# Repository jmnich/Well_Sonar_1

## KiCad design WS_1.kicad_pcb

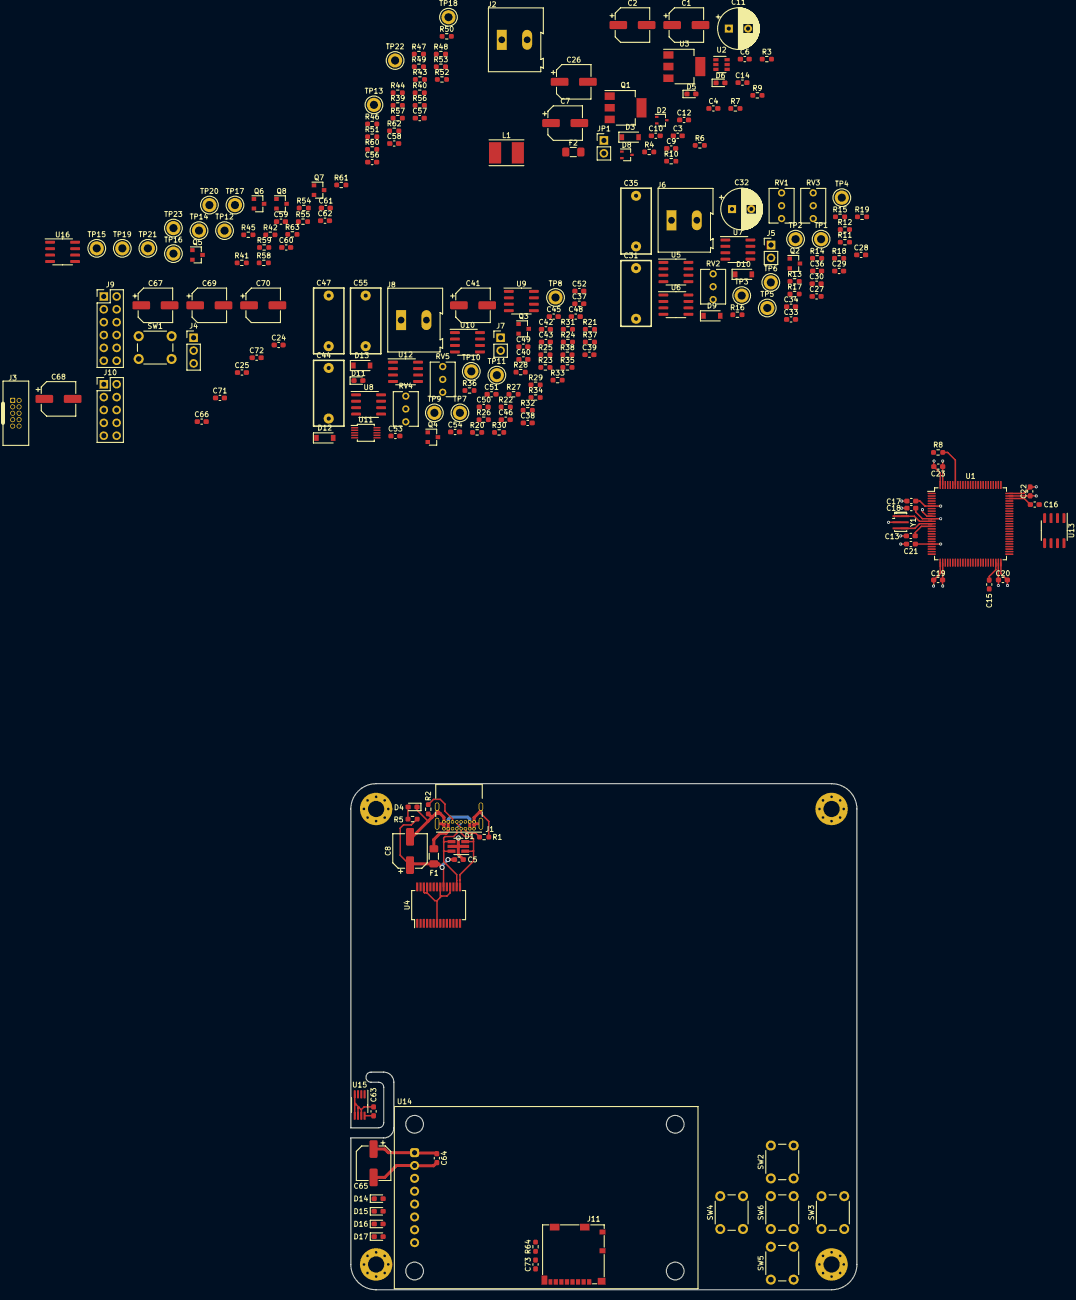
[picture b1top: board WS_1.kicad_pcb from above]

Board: 4 copper layers, 100.0 x 100.0 mm, 231 parts (0 on the bottom side), 138 nets.

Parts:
C1, C2, C7, C8, C26, C41, C65, C67, C68, C69, C70: 56u 25V; CP_Elec_6.3x5.9
C3, C4, C6, C12, C14, C17, C18, C19, C20, C21, C22, C23, C24, C25, C49, C52, C66, C71, C72: 1u; C_0603_1608Metric_Pad1.05x0.95mm_HandSolder
C5, C13, C37, C40, C45, C56, C57, C58, C59, C60, C61, C62, C63, C64, C73: 100n; C_0603_1608Metric_Pad1.05x0.95mm_HandSolder
C9: 10p 50V; C_0603_1608Metric_Pad1.05x0.95mm_HandSolder
C10, C30, C33, C36: 1u 50V; C_0603_1608Metric_Pad1.05x0.95mm_HandSolder
C11, C32: 220u 35V; CP_Radial_D8.0mm_P3.80mm
C15, C16: 2u2; C_0603_1608Metric_Pad1.05x0.95mm_HandSolder
C27, C28, C29: 10n 50V; C_0603_1608Metric_Pad1.05x0.95mm_HandSolder
C31, C35, C47, C55: 100n MKT; MKT_L13xW6xH12_p10
C34: 100p; C_0603_1608Metric_Pad1.05x0.95mm_HandSolder
C38, C39, C43, C54: 10n; C_0603_1608Metric_Pad1.05x0.95mm_HandSolder
C42: 100n 50V; C_0603_1608Metric_Pad1.05x0.95mm_HandSolder
C44: 1n MKT; MKT_L13xW6xH12_p10
C46, C48, C50, C51, C53: DNP; C_0603_1608Metric_Pad1.05x0.95mm_HandSolder
D1: ESDA6V1BC6; SOT-23-6_Handsoldering
D2, D8: BAT54W; SOT-323_SC-70
D3, D9, D10, D12, D13: MBR0530T1G; D_SOD-123
D4, D5, D6, D11, D14, D15, D16, D17: LED_G; LED_0603_1608Metric_Pad1.05x0.95mm_HandSolder
F1, F2: Fuse 2.5A; Fuse_1206_3216Metric_Pad1.42x1.75mm_HandSolder
H1, H2, H3, H4: MountingHole; MountingHole_3.2mm_M3_Pad_Via
J1: USB_C_Receptacle_USB2.0; USB_C_Receptacle_GCT_USB4085
J2, J6, J8: WE_691216710002
J3: SWD; 10pin_1.27_socket
J4: BOOT_SEL; PinHeader_1x03_P2.54mm_Vertical
J5, J7: T_OUT; PinHeader_1x02_P2.54mm_Vertical
J9: EXT_CONN_A; PinHeader_2x06_P2.54mm_Vertical
J10: EXT_CONN_B; PinHeader_2x05_P2.54mm_Vertical
J11: Micro_SD_Card; Molex_104031-0811
JP1: NC; PinHeader_1x02_P2.54mm_Vertical
L1: 10uH 2A; L_Taiyo-Yuden_NR-50xx_HandSoldering
Q1: IRLL014NPBF; SOT-223
Q2, Q3, Q4, Q5, Q6, Q7, Q8: 2N7002; SOT-23
R1, R2: 5k1 5%; R_0603_1608Metric_Pad0.98x0.95mm_HandSolder
R3, R9, R11, R12, R14, R28, R34, R35: 100k 1%; R_0603_1608Metric_Pad0.98x0.95mm_HandSolder
R4: 3k6 1%; R_0603_1608Metric_Pad0.98x0.95mm_HandSolder
R5, R6, R7, R39, R40, R41, R42: 20k 5%; R_0603_1608Metric_Pad0.98x0.95mm_HandSolder
R8, R23, R29, R30, R47, R48, R49, R50, R56, R57, R58, R59, R60, R63, R64: 47k 5%; R_0603_1608Metric_Pad0.98x0.95mm_HandSolder
R10: 0R; R_0603_1608Metric_Pad0.98x0.95mm_HandSolder
R13, R18: 5k1 1%; R_0603_1608Metric_Pad0.98x0.95mm_HandSolder
R15, R16, R17, R19, R32: 1k 1%; R_0603_1608Metric_Pad0.98x0.95mm_HandSolder
R20, R22, R43, R44, R45, R46: 10k 5%; R_0603_1608Metric_Pad0.98x0.95mm_HandSolder
R21, R24: 1k 5%; R_0603_1608Metric_Pad0.98x0.95mm_HandSolder
R25: 22k 1%; R_0603_1608Metric_Pad0.98x0.95mm_HandSolder
R26, R33: 1Meg 1%; R_0603_1608Metric_Pad0.98x0.95mm_HandSolder
R27: 470k 1%; R_0603_1608Metric_Pad0.98x0.95mm_HandSolder
R31: 20k 1%; R_0603_1608Metric_Pad0.98x0.95mm_HandSolder
R36, R37: 47k 1%; R_0603_1608Metric_Pad0.98x0.95mm_HandSolder
R38: DNP; R_0603_1608Metric_Pad0.98x0.95mm_HandSolder
R51, R52, R53, R54, R55: 100R 5%; R_0603_1608Metric_Pad0.98x0.95mm_HandSolder
R61, R62: 2k2 1%; R_0603_1608Metric_Pad0.98x0.95mm_HandSolder
RV1, RV2, RV3, RV4, RV5: 10k; Potentiometer_Vishay_T73XW_Horizontal
SW1, SW2, SW3, SW4, SW5, SW6: SW; SW_PUSH_6mm_H4.3mm
TP1, TP2, TP3, TP4, TP5, TP6, TP7, TP8, TP9, TP10, TP11, TP12, TP13, TP14, TP15, TP16, TP17, TP18, TP19, TP20, TP21, TP22, TP23: Test Point; TestPoint_Keystone_5010-5014_Multipurpose
U1: STM32H743VITx; LQFP-100_14x14mm_P0.5mm
U2: MT3608; SOT-23-6
U3: AMS1117-3.3; SOT-223-3_TabPin2
U4: FT232RL; SSOP-28_5.3x10.2mm_P0.65mm
U5, U7, U8, U9: AD823; SOIC-8_3.9x4.9mm_P1.27mm
U6: LM393; SOIC-8_3.9x4.9mm_P1.27mm
U10: LM567; SOIC-8_3.9x4.9mm_P1.27mm
U11: MAX4734EUB+; MSOP-10_3x3mm_P0.5mm
U12: LM4140ACM-2.0; SOIC-8_3.9x4.9mm_P1.27mm
U13: IS25LP032D; SOIC-8_3.9x4.9mm_P1.27mm
U14: Waveshare_LCD_1_8; Waveshare_LCD_1.8
U15: MCP9808_MSOP; MSOP-8_3x3mm_P0.65mm
U16: M24256-BR; SOIC-8_3.9x4.9mm_P1.27mm
Y1: 10MHz; Resonator_SMD_muRata_CSTxExxV-3Pin_3.0x1.1mm_HandSoldering

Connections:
+3V3: C6.1, C7.1, C17.1, C18.1, C19.1, C20.1, C21.1, C22.1, C23.1, C24.1, C25.1, C37.1, C40.1, C41.1, C45.1, C49.1, C61.1, C62.1, C63.1, C64.1, C65.1, C66.1, C67.1, C68.1, C73.1, D2.1, D12.1, J3.1, J4.1, J9.1, J10.1, J11.4, R18.1, R19.1, R20.1, R22.1, R56.2, R57.2, R58.2, R59.2, R60.2, R61.2, R62.2, R63.2, R64.2, U1.6, U1.11, U1.21, U1.27, U1.50, U1.75, U1.100, U3.2, U8.8, U9.8, U11.5, U11.6, U12.2, U12.3, U13.8, U14.1, U15.8, U16.8
+5V: C1.1, C2.1, C3.1, C4.1, C26.1, C42.1, C69.1, C70.1, C71.1, C72.1, D2.3, F2.1, J9.2, J10.2, JP1.1, L1.1, R9.2, R23.1, R39.1, R40.1, R41.1, R42.1, U2.4, U2.5, U3.3, U10.4
/BOOT0: R8.1, U1.94
/BUT_1: R51.1, R56.1, U1.85
/BUT_2: R52.1, R57.1, U1.86
/BUT_3: R53.1, R58.1, U1.87
/BUT_4: R54.1, R59.1, U1.88
/BUT_5: R55.1, R60.1, U1.55
/DDS_IN: U1.28, U5.3
/DET_OUTPUT: Q3.3, R20.2, R24.1, TP10.1, U1.30
/EEP_~WC: U1.54, U16.7
/FLASH_IO0: U1.58, U13.5
/FLASH_IO1: U1.59, U13.2
/FLASH_IO2: U1.1, U13.3
/FLASH_IO3: U1.60, U13.7
/FLASH_SCK: U1.36, U13.6
/FLASH_~CE: U1.46, U13.1
/FT_RX: U1.22, U4.5
/FT_TX: U1.23, U4.1
/GAIN_SEL_A0: R30.1, U1.24, U11.1
/GAIN_SEL_A1: R29.1, U1.25, U11.10
/LCD_BL: TP23.1, U1.71, U14.8
/LCD_CLK: TP19.1, U1.78, U14.4
/LCD_CS: TP20.1, U1.77, U14.5
/LCD_DC: TP21.1, U1.69, U14.6
/LCD_DIN: TP18.1, U1.80, U14.3
/LCD_RST: TP22.1, U1.70, U14.7
/LED_1: R43.1, R47.2, TP12.1, U1.81
/LED_2: R44.1, R48.2, TP13.1, U1.82
/LED_3: R45.1, R49.2, TP14.1, U1.83
/LED_4: R46.1, R50.2, TP15.1, U1.84
/NRST: C13.1, J3.10, SW1.2, U1.14
/OUT_WIND_BREACH: Q2.3, R19.2, TP1.1, U1.52
/PA5: J9.6, U1.29
/PA8: J10.6, U1.67
/PB0: J9.5, U1.34
/PB1: J9.7, U1.35
/PC2: J10.9, U1.17
/PC3: J10.10, U1.18
/PC4: J9.9, U1.32
/PC5: J9.11, U1.33
/PC9: J10.8, U1.66
/PE0: J10.5, U1.97
/PE1: J10.7, U1.98
/PE7: J9.8, U1.37
/PE8: J9.10, U1.38
/PE9: J9.12, U1.39
/RAW_OUTPUT: C46.1, C47.1, C48.1, C50.1, C51.1, R26.2, R27.2, R28.2, R31.2, TP11.1, U1.31, U7.1
/SCL: R61.1, TP17.1, U1.92, U15.2, U16.6
/SDA: R62.1, TP16.1, U1.93, U15.1, U16.5
/SD_CLK: J11.5, U1.42
/SD_CS: J11.2, R64.1, U1.3
/SD_MISO: J11.7, U1.4
/SD_MOSI: J11.3, U1.5
/SWDCLK: J3.4, U1.76
/SWDIO: J3.2, U1.72
/SWO: J3.6, U1.89
/TH_ALERT: R63.1, U1.53, U15.3
/VREF: R35.1, TP7.1, U1.20, U8.1, U8.2
/in frontend/0.5_VREF: TP8.1, U7.3, U7.5, U8.6, U8.7
/in frontend/FREQ_TEST: RV4.1, TP9.1, U10.5
/out frontend/DDS: C31.2, TP4.1, U5.1, U5.2
/out frontend/DDS_AC: C31.1, R16.1, TP6.1
/out frontend/DRIVE_REF: C27.1, R11.1, R12.2, TP2.1, U5.5
/out frontend/T_OUT_AC: C35.1, J5.1, J6.1, TP3.1
/out frontend/T_OUT_DC: C34.1, C35.2, D9.2, D10.1, RV3.3, TP5.1, U5.7, U6.2, U6.5
/power/DN: D1.4, D1.6, J1.A7, J1.B7, U4.16
/power/DP: D1.1, D1.3, J1.A6, J1.B6, U4.15
/power/FT3V3: C12.1, R6.2, R7.2, U4.4, U4.17
GND: C1.2, C2.2, C3.2, C4.2, C5.2, C6.2, C7.2, C8.2, C10.2, C11.2, C12.2, C13.2, C14.2, C15.2, C16.2, C17.2, C18.2, C19.2, C20.2, C21.2, C22.2, C23.2, C24.2, C25.2, C26.2, C27.2, C28.2, C29.2, C30.2, C32.2, C33.2, C36.2, C37.2, C38.2, C39.2, C40.2, C41.2, C42.2, C43.2, C44.1, C45.2, C49.2, C52.2, C54.2, C56.2, C57.2, C58.2, C59.2, C60.2, C61.2, C62.2, C63.2, C64.2, C65.2, C66.2, C67.2, C68.2, C69.2, C70.2, C71.2, C72.2, C73.2, D1.2, D1.5, D4.1, D8.1, D10.2, D13.2, J1.A1, J1.A12, J1.B1, J1.B12, J1.S1, J3.3, J3.5, J3.9, J4.3, J5.2, J6.2, J7.2, J8.2, J9.3, J9.4, J10.3, J10.4, J11.6, J11.9, Q1.3, Q2.2, Q3.2, Q4.2, Q5.2, Q6.2, Q7.2, Q8.2, R1.1, R2.1, R10.1, R12.1, R15.2, R29.2, R30.2, R38.2, R47.1, R48.1, R49.1, R50.1, RV5.2, RV5.3, SW1.1, SW2.1, SW3.1, SW4.1, SW5.1, SW6.1, U1.10, U1.19, U1.26, U1.49, U1.74, U1.99, U2.2, U3.1, U4.7, U4.18, U4.21, U4.25, U4.26, U5.4, U6.4, U7.4, U8.4, U9.4, U10.7, U11.3, U12.1, U12.4, U12.7, U12.8, U13.4, U14.2, U15.4, U15.5, U15.6, U15.7, U16.1, U16.2, U16.3, U16.4, Y1.2
unnamed: C9.2, R3.1, R4.2, U2.3
unnamed: C15.1, U1.48
unnamed: C16.1, U1.73
unnamed: C28.1, R14.1, RV1.2, RV1.3, U6.3
unnamed: C29.1, R14.2, RV2.1, U6.6
unnamed: C34.2, R16.2, R17.1, U5.6
unnamed: C38.1, C39.1, U10.1
unnamed: C43.1, U10.2
unnamed: C44.2, R25.1, RV4.2, RV4.3
unnamed: C46.2, R26.1, U11.7
unnamed: C47.2, U10.3
unnamed: C48.2, R27.1, U11.4
unnamed: C50.2, R28.1, U11.9
unnamed: C51.2, R31.1, U11.2
unnamed: C52.1, U8.3, U12.6
unnamed: C53.1, R33.1, R34.2, U7.6
unnamed: C53.2, R32.1, R33.2, U7.7
unnamed: C54.1, R35.2, R36.1, U8.5
unnamed: C55.1, J7.1, J8.1, R38.1
unnamed: C55.2, D12.2, D13.1, R34.1
unnamed: C56.1, R51.2, SW2.2
unnamed: C57.1, R52.2, SW3.2
unnamed: C58.1, R53.2, SW4.2
unnamed: C59.1, R54.2, SW5.2
unnamed: C60.1, R55.2, SW6.2
unnamed: D3.2, L1.2, U2.1
unnamed: D4.2, R5.1
unnamed: D5.1, U4.23
unnamed: D5.2, R6.1
unnamed: D6.1, U4.22
unnamed: D6.2, R7.1
unnamed: D8.3, Q1.1, R9.1
unnamed: D11.1, Q4.3
unnamed: D11.2, R23.2
unnamed: D14.1, Q5.3
unnamed: D14.2, R39.2
unnamed: D15.1, Q6.3
unnamed: D15.2, R40.2
unnamed: D16.1, Q7.3
unnamed: D16.2, R41.2
unnamed: D17.1, Q8.3
unnamed: D17.2, R42.2
unnamed: F1.2, J1.A4, J1.A9, J1.B4, J1.B9
unnamed: F2.2, J2.1
unnamed: J1.A5, R1.2
unnamed: J1.B5, R2.2
unnamed: J2.2, Q1.2, Q1.4
unnamed: J4.2, R8.2
unnamed: Q2.1, R18.2, U6.1, U6.7
unnamed: Q3.1, R21.2
unnamed: Q4.1, R24.2
unnamed: Q5.1, R43.2
unnamed: Q6.1, R44.2
unnamed: Q7.1, R45.2
unnamed: Q8.1, R46.2
unnamed: R4.1, R10.2
unnamed: R13.2, RV1.1
unnamed: R15.1, RV2.2, RV2.3
unnamed: R17.2, RV3.1, RV3.2
unnamed: R21.1, R22.2, U10.8
unnamed: R25.2, U10.6
unnamed: R32.2, U7.2, U11.8
unnamed: R36.2, R37.1
unnamed: R37.2, RV5.1
unnamed: U1.12, Y1.1
unnamed: U1.13, Y1.3
VBUS: C5.1, C8.1, C14.1, F1.1, JP1.2, R5.2, U4.20
Vdrive: C9.1, C10.1, C11.1, C30.1, C32.1, C33.1, C36.1, D3.1, D9.1, R3.2, R11.2, R13.1, U5.8, U6.8, U7.8
